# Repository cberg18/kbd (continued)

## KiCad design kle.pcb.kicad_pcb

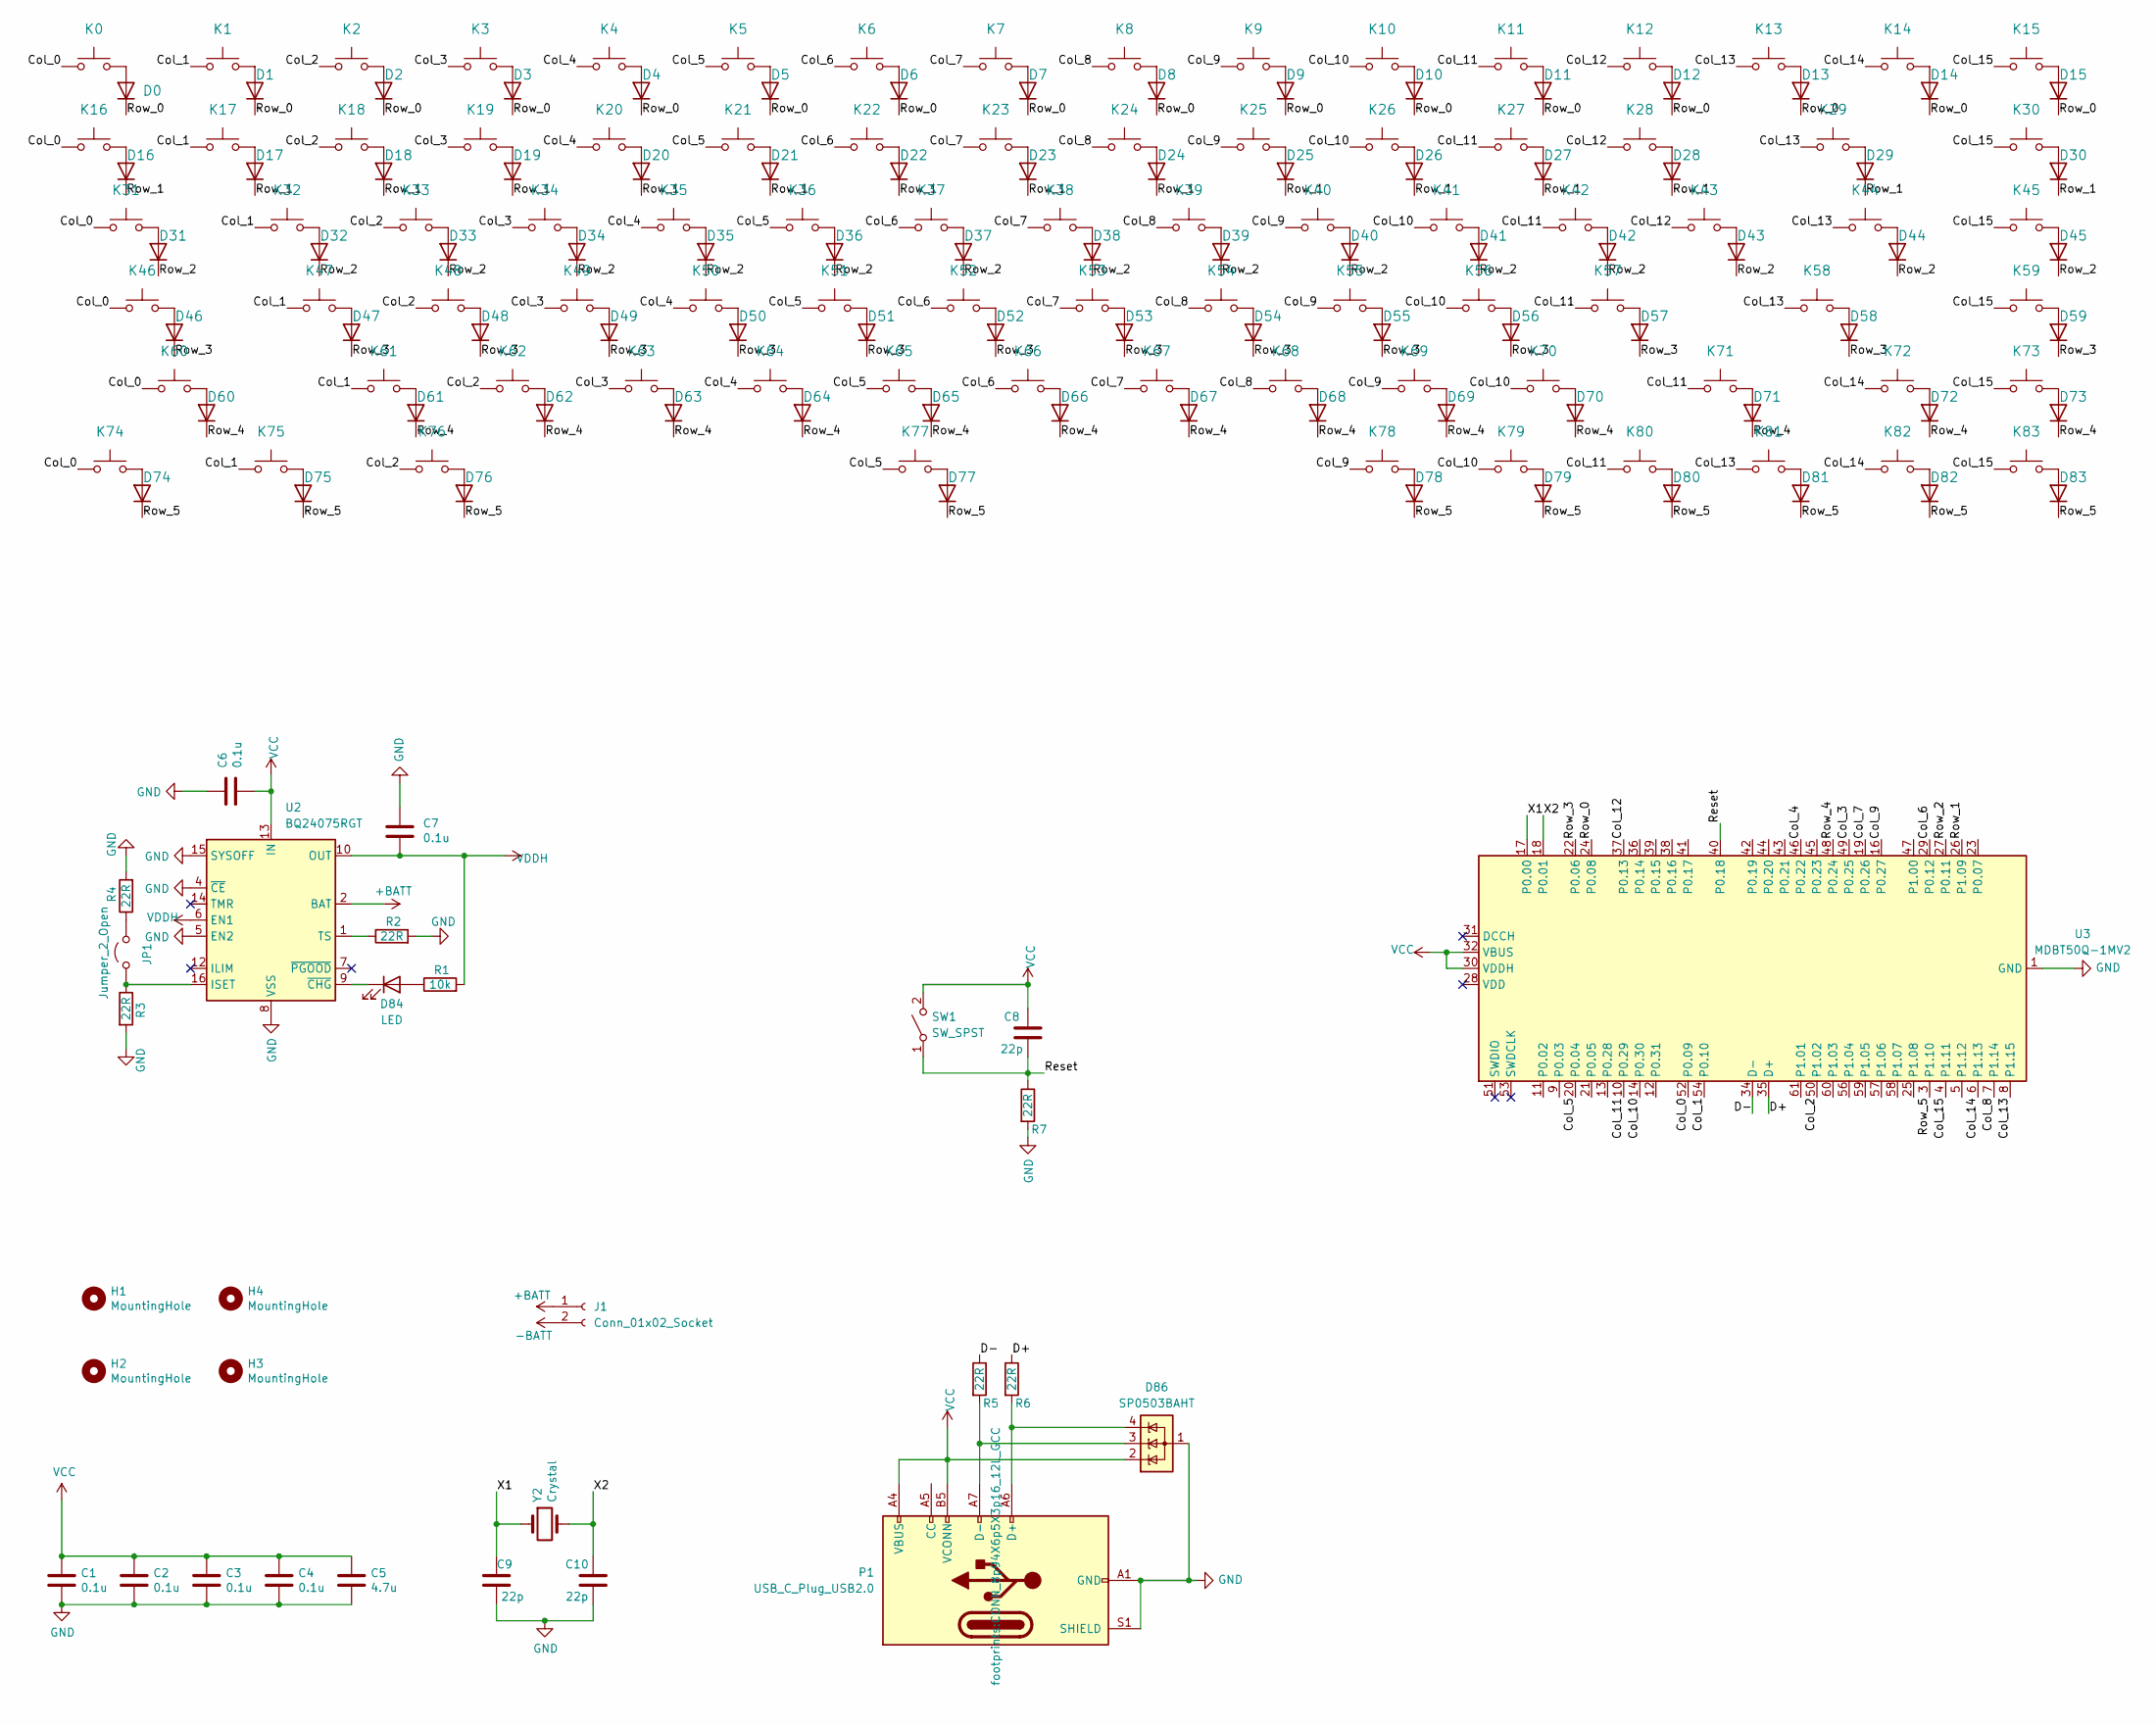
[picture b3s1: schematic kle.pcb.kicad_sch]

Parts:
C1, C2, C3, C4, C6, C7: 0.1u; C_0805_2012Metric_Pad1.15x1.40mm_HandSolder
C5: 4.7u; C_0805_2012Metric_Pad1.15x1.40mm_HandSolder
C8, C9, C10: 22p; C_0805_2012Metric_Pad1.15x1.40mm_HandSolder
D0, D1, D2, D3, D4, D5, D6, D7, D8, D9, D10, D11, D12, D13, D14, D15, D16, D17, D18, D19, D20, D21, D22, D23, D24, D25, D26, D27, D28, D29, D30, D31, D32, D33, D34, D35, D36, D37, D38, D39, D40, D41, D42, D43, D44, D45, D46, D47, D48, D49, D50, D51, D52, D53, D54, D55, D56, D57, D58, D59, D60, D61, D62, D63, D64, D65, D66, D67, D68, D69, D70, D71, D72, D73, D74, D75, D76, D77, D78, D79, D80, D81, D82, D83: D; D_0805_2012Metric_Pad1.15x1.40mm_HandSolder
D84: LED; LED_0805_2012Metric_Pad1.15x1.40mm_HandSolder
D86: SP0503BAHT; SOT-143
H1, H2, H3, H4: MountingHole; MountingHole_3.2mm_M3_DIN965_Pad
J1: Conn_01x02_Socket; JST_EH_S2B-EH_1x02_P2.50mm_Horizontal
JP1: Jumper_2_Open; SolderJumper-2_P1.3mm_Open_TrianglePad1.0x1.5mm
K0: Esc; MX-Hotswap-1U
K1: F1; MX-Hotswap-1U
K2: F2; MX-Hotswap-1U
K3: F3; MX-Hotswap-1U
K4: F4; MX-Hotswap-1U
K5: F5; MX-Hotswap-1U
K6: F6; MX-Hotswap-1U
K7: F7; MX-Hotswap-1U
K8: F8; MX-Hotswap-1U
K9: F9; MX-Hotswap-1U
K10: F10; MX-Hotswap-1U
K11: F11; MX-Hotswap-1U
K12: F12; MX-Hotswap-1U
K13: PrtSc,NmLk; MX-Hotswap-1U
K14: Pause,ScrLk; MX-Hotswap-1U
K15: Delete,Insert; MX-Hotswap-1U
K16: ~~,`; MX-Hotswap-1U
K17: !,1; MX-Hotswap-1U
K18: @,2; MX-Hotswap-1U
K19: #,3; MX-Hotswap-1U
K20: $,4; MX-Hotswap-1U
K21: %,5; MX-Hotswap-1U
K22: ^,6; MX-Hotswap-1U
K23: &,7; MX-Hotswap-1U
K24: *,8; MX-Hotswap-1U
K25: (,9; MX-Hotswap-1U
K26: ),0; MX-Hotswap-1U
K27: _,-; MX-Hotswap-1U
K28: +,=; MX-Hotswap-1U
K29: Backspace; MX-Hotswap-2U
K30: Home; MX-Hotswap-1U
K31: Tab; MX-Hotswap-1.5U
K32: Q; MX-Hotswap-1U
K33: W; MX-Hotswap-1U
K34: E; MX-Hotswap-1U
K35: R; MX-Hotswap-1U
K36: T; MX-Hotswap-1U
K37: Y; MX-Hotswap-1U
K38: U; MX-Hotswap-1U
K39: I; MX-Hotswap-1U
K40: O; MX-Hotswap-1U
K41: P; MX-Hotswap-1U
K42: {,[; MX-Hotswap-1U
K43: },]; MX-Hotswap-1U
K44: |,\; MX-Hotswap-1.5U
K45: Page Up; MX-Hotswap-1U
K46: Caps Lock; MX-Hotswap-1.75U
K47: A; MX-Hotswap-1U
K48: S; MX-Hotswap-1U
K49: D; MX-Hotswap-1U
K50: F; MX-Hotswap-1U
K51: G; MX-Hotswap-1U
K52: H; MX-Hotswap-1U
K53: J; MX-Hotswap-1U
K54: K; MX-Hotswap-1U
K55: L; MX-Hotswap-1U
K56: :,;; MX-Hotswap-1U
K57: ",'; MX-Hotswap-1U
K58: Enter; MX-Hotswap-2.25U
K59: Page Down; MX-Hotswap-1U
K60: Shift; MX-Hotswap-2.25U
K61: Z; MX-Hotswap-1U
K62: X; MX-Hotswap-1U
K63: C; MX-Hotswap-1U
K64: V; MX-Hotswap-1U
K65: B; MX-Hotswap-1U
K66: N; MX-Hotswap-1U
K67: M; MX-Hotswap-1U
K68: <,,; MX-Hotswap-1U
K69: >,.; MX-Hotswap-1U
K70: ?,/; MX-Hotswap-1U
K71: Shift; MX-Hotswap-1.75U
K72: ↑; MX-Hotswap-1U
K73: End; MX-Hotswap-1U
K74: Ctrl; MX-Hotswap-1.25U
K75: Lin; MX-Hotswap-1.25U
K76: Alt; MX-Hotswap-1.25U
K77: Space; MX-Hotswap-6.25U
K78: Alt; MX-Hotswap-1U
K79: Fn; MX-Hotswap-1U
K80: Ctrl; MX-Hotswap-1U
K81: ←; MX-Hotswap-1U
K82: ↓; MX-Hotswap-1U
K83: →; MX-Hotswap-1U
P1: USB_C_Plug_USB2.0; CONN_8p94X6p5X3p16_12L_GCC
R1: 10k; R_0805_2012Metric_Pad1.20x1.40mm_HandSolder
R2, R3, R4, R5, R6, R7: 22R; R_0805_2012Metric_Pad1.20x1.40mm_HandSolder
SW1: SW_SPST; SW_SPST_TS-1088-xR025
U2: BQ24075RGT; VQFN-16-1EP_3x3mm_P0.5mm_EP1.6x1.6mm
U3: MDBT50Q-1MV2; Raytac_MDBT50Q
Y2: Crystal; Crystal_SMD_2012-2Pin_2.0x1.2mm_HandSoldering

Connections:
+BATT: J1.1, U2.2 (BAT), U2.3 (BAT)
-BATT: J1.2
/Col_0: K0.1, K16.1, K31.1, K46.1, K60.1, K74.1, U3.52 (P0.09)
/Col_1: K1.1, K17.1, K32.1, K47.1, K61.1, K75.1, U3.54 (P0.10)
/Col_2: K2.1, K18.1, K33.1, K48.1, K62.1, K76.1, U3.50 (P1.02)
/Col_3: K3.1, K19.1, K34.1, K49.1, K63.1, U3.49 (P0.25)
/Col_4: K4.1, K20.1, K35.1, K50.1, K64.1, U3.46 (P0.22)
/Col_5: K5.1, K21.1, K36.1, K51.1, K65.1, K77.1, U3.20 (P0.04)
/Col_6: K6.1, K22.1, K37.1, K52.1, K66.1, U3.29 (P0.12)
/Col_7: K7.1, K23.1, K38.1, K53.1, K67.1, U3.19 (P0.26)
/Col_8: K8.1, K24.1, K39.1, K54.1, K68.1, U3.7 (P1.14)
/Col_9: K9.1, K25.1, K40.1, K55.1, K69.1, K78.1, U3.16 (P0.27)
/Col_10: K10.1, K26.1, K41.1, K56.1, K70.1, K79.1, U3.14 (P0.30)
/Col_11: K11.1, K27.1, K42.1, K57.1, K71.1, K80.1, U3.10 (P0.29)
/Col_12: K12.1, K28.1, K43.1, U3.37 (P0.13)
/Col_13: K13.1, K29.1, K44.1, K58.1, K81.1, U3.8 (P1.15)
/Col_14: K14.1, K72.1, K82.1, U3.6 (P1.13)
/Col_15: K15.1, K30.1, K45.1, K59.1, K73.1, K83.1, U3.4 (P1.11)
/D+: R6.1, U3.35 (D+)
/D-: R5.1, U3.34 (D-)
/Reset: C8.2, R7.1, SW1.1 (A), U3.40 (P0.18)
/Row_0: D0.1 (K), D1.1 (K), D2.1 (K), D3.1 (K), D4.1 (K), D5.1 (K), D6.1 (K), D7.1 (K), D8.1 (K), D9.1 (K), D10.1 (K), D11.1 (K), D12.1 (K), D13.1 (K), D14.1 (K), D15.1 (K), U3.24 (P0.08)
/Row_1: D16.1 (K), D17.1 (K), D18.1 (K), D19.1 (K), D20.1 (K), D21.1 (K), D22.1 (K), D23.1 (K), D24.1 (K), D25.1 (K), D26.1 (K), D27.1 (K), D28.1 (K), D29.1 (K), D30.1 (K), U3.26 (P1.09)
/Row_2: D31.1 (K), D32.1 (K), D33.1 (K), D34.1 (K), D35.1 (K), D36.1 (K), D37.1 (K), D38.1 (K), D39.1 (K), D40.1 (K), D41.1 (K), D42.1 (K), D43.1 (K), D44.1 (K), D45.1 (K), U3.27 (P0.11)
/Row_3: D46.1 (K), D47.1 (K), D48.1 (K), D49.1 (K), D50.1 (K), D51.1 (K), D52.1 (K), D53.1 (K), D54.1 (K), D55.1 (K), D56.1 (K), D57.1 (K), D58.1 (K), D59.1 (K), U3.22 (P0.06)
/Row_4: D60.1 (K), D61.1 (K), D62.1 (K), D63.1 (K), D64.1 (K), D65.1 (K), D66.1 (K), D67.1 (K), D68.1 (K), D69.1 (K), D70.1 (K), D71.1 (K), D72.1 (K), D73.1 (K), U3.48 (P0.24)
/Row_5: D74.1 (K), D75.1 (K), D76.1 (K), D77.1 (K), D78.1 (K), D79.1 (K), D80.1 (K), D81.1 (K), D82.1 (K), D83.1 (K), U3.3 (P1.10)
/X1: C9.1, U3.17 (P0.00), Y2.1
/X2: C10.1, U3.18 (P0.01), Y2.2
GND: C1.2, C2.2, C3.2, C4.2, C5.2, C6.2, C7.2, C9.2, C10.2, D86.1 (A), P1.A1 (GND), P1.A12 (GND), P1.B1 (GND), P1.B12 (GND), P1.S1 (SHIELD), R2.2, R3.2, R4.2, R7.2, U2.4 (~CE), U2.5 (EN2), U2.8 (VSS), U2.15 (SYSOFF), U2.17 (VSS), U3.1 (GND), U3.2 (GND), U3.15 (GND), U3.33 (GND), U3.55 (GND)
unnamed: D0.2 (A), K0.2
unnamed: D1.2 (A), K1.2
unnamed: D2.2 (A), K2.2
unnamed: D3.2 (A), K3.2
unnamed: D4.2 (A), K4.2
unnamed: D5.2 (A), K5.2
unnamed: D6.2 (A), K6.2
unnamed: D7.2 (A), K7.2
unnamed: D8.2 (A), K8.2
unnamed: D9.2 (A), K9.2
unnamed: D10.2 (A), K10.2
unnamed: D11.2 (A), K11.2
unnamed: D12.2 (A), K12.2
unnamed: D13.2 (A), K13.2
unnamed: D14.2 (A), K14.2
unnamed: D15.2 (A), K15.2
unnamed: D16.2 (A), K16.2
unnamed: D17.2 (A), K17.2
unnamed: D18.2 (A), K18.2
unnamed: D19.2 (A), K19.2
unnamed: D20.2 (A), K20.2
unnamed: D21.2 (A), K21.2
unnamed: D22.2 (A), K22.2
unnamed: D23.2 (A), K23.2
unnamed: D24.2 (A), K24.2
unnamed: D25.2 (A), K25.2
unnamed: D26.2 (A), K26.2
unnamed: D27.2 (A), K27.2
unnamed: D28.2 (A), K28.2
unnamed: D29.2 (A), K29.2
unnamed: D30.2 (A), K30.2
unnamed: D31.2 (A), K31.2
unnamed: D32.2 (A), K32.2
unnamed: D33.2 (A), K33.2
unnamed: D34.2 (A), K34.2
unnamed: D35.2 (A), K35.2
unnamed: D36.2 (A), K36.2
unnamed: D37.2 (A), K37.2
unnamed: D38.2 (A), K38.2
unnamed: D39.2 (A), K39.2
unnamed: D40.2 (A), K40.2
unnamed: D41.2 (A), K41.2
unnamed: D42.2 (A), K42.2
unnamed: D43.2 (A), K43.2
unnamed: D44.2 (A), K44.2
unnamed: D45.2 (A), K45.2
unnamed: D46.2 (A), K46.2
unnamed: D47.2 (A), K47.2
unnamed: D48.2 (A), K48.2
unnamed: D49.2 (A), K49.2
unnamed: D50.2 (A), K50.2
unnamed: D51.2 (A), K51.2
unnamed: D52.2 (A), K52.2
unnamed: D53.2 (A), K53.2
unnamed: D54.2 (A), K54.2
unnamed: D55.2 (A), K55.2
unnamed: D56.2 (A), K56.2
unnamed: D57.2 (A), K57.2
unnamed: D58.2 (A), K58.2
unnamed: D59.2 (A), K59.2
unnamed: D60.2 (A), K60.2
unnamed: D61.2 (A), K61.2
unnamed: D62.2 (A), K62.2
unnamed: D63.2 (A), K63.2
unnamed: D64.2 (A), K64.2
unnamed: D65.2 (A), K65.2
unnamed: D66.2 (A), K66.2
unnamed: D67.2 (A), K67.2
unnamed: D68.2 (A), K68.2
unnamed: D69.2 (A), K69.2
unnamed: D70.2 (A), K70.2
unnamed: D71.2 (A), K71.2
unnamed: D72.2 (A), K72.2
unnamed: D73.2 (A), K73.2
unnamed: D74.2 (A), K74.2
unnamed: D75.2 (A), K75.2
unnamed: D76.2 (A), K76.2
unnamed: D77.2 (A), K77.2
unnamed: D78.2 (A), K78.2
unnamed: D79.2 (A), K79.2
unnamed: D80.2 (A), K80.2
unnamed: D81.2 (A), K81.2
unnamed: D82.2 (A), K82.2
unnamed: D83.2 (A), K83.2
unnamed: D84.2 (A), R1.1
unnamed: D84.1 (K), U2.9 (~CHG)
unnamed: JP1.1 (A), R3.1, U2.16 (ISET)
unnamed: JP1.2 (B), R4.1
unnamed: D86.4 (K), P1.A6 (D+), R6.2
unnamed: D86.3 (K), P1.A7 (D-), R5.2
unnamed: R2.1, U2.1 (TS)
VCC: C1.1, C2.1, C3.1, C4.1, C5.1, C6.1, C8.1, D86.2 (K), P1.A4 (VBUS), P1.A9 (VBUS), P1.B4 (VBUS), P1.B5 (VCONN), P1.B9 (VBUS), SW1.2 (B), U2.13 (IN), U3.30 (VDDH), U3.32 (VBUS)
VDDH: C7.1, R1.2, U2.6 (EN1), U2.10 (OUT), U2.11 (OUT)

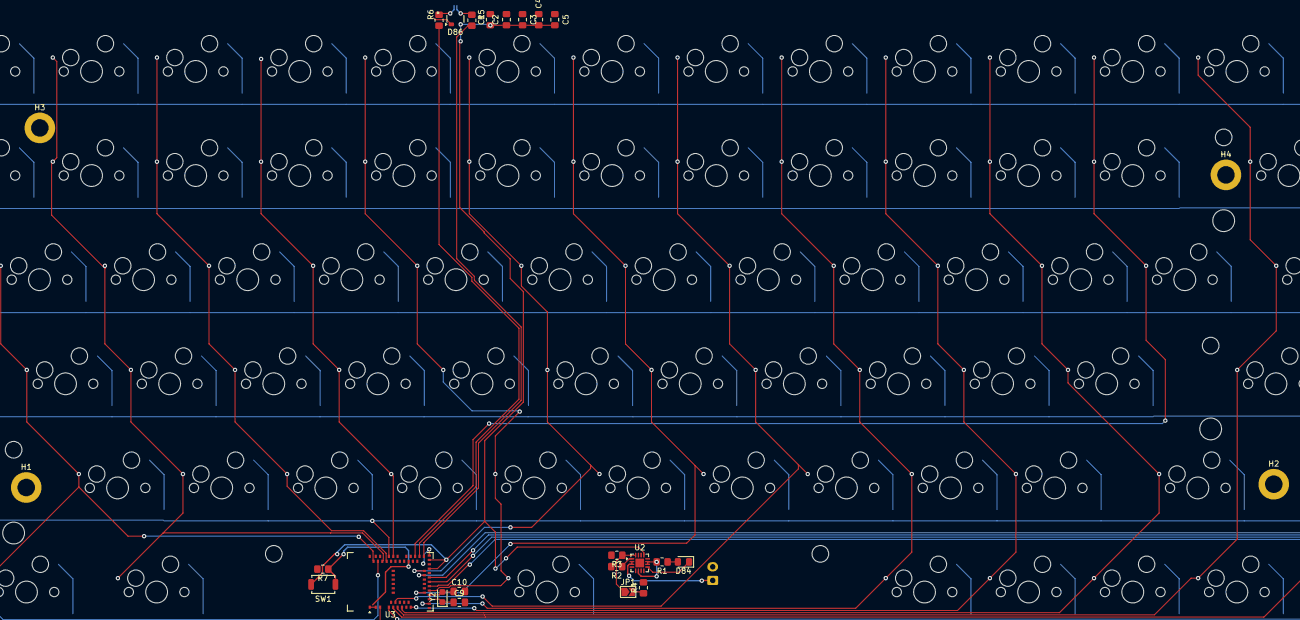
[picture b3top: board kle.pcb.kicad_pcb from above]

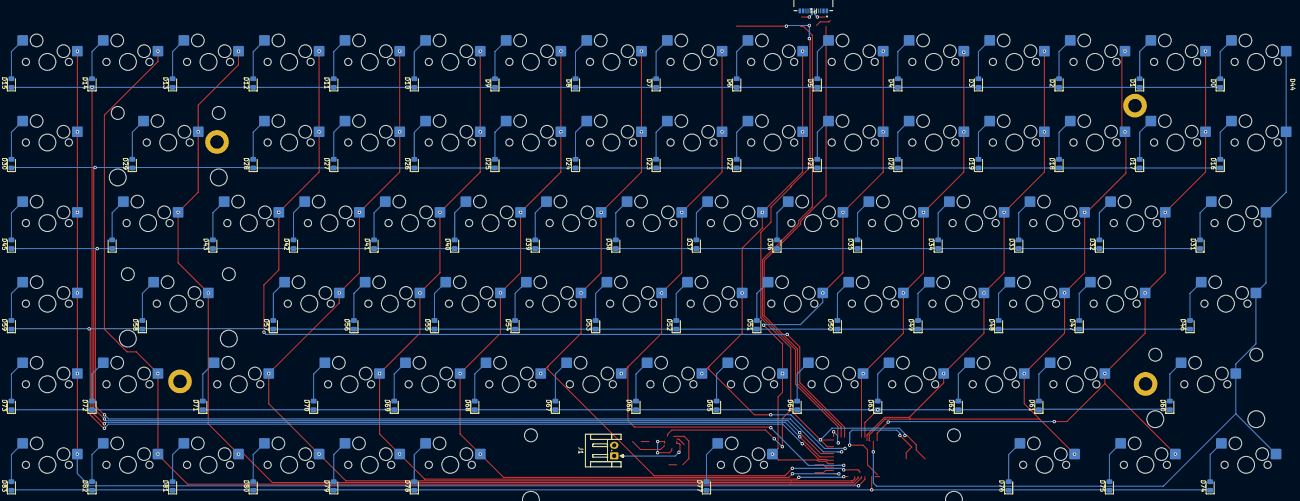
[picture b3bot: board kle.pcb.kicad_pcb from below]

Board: 2 copper layers, 195 parts (170 on the bottom side), 122 nets.

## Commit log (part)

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2026-02-02 init
2026-02-04 tweak layout
2026-02-06 progress
2026-02-06 new ignores
2026-02-08 add battery connector
2026-02-08 save footprint positions
2026-02-12 fix board generation
2026-02-17 add usb bump
